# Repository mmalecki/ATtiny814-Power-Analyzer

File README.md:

# Pocker Power Prowler

**Note: this is still very much a work in progress, and next version will bring considerable improvements over the current one.**

Pocket Power Prowler is a tiny programmable constant current dummy load with voltage and current sensors for test device's power supply, as well as its output under test.

It is programmable via USB using a simple text-based protocol, and [in the future](https://github.com/mmalecki/Pocket-Power-Prowler/issues/4)), the [SCPI protocol](https://en.wikipedia.org/wiki/Standard_Commands_for_Programmable_Instruments).

It is based on the [ATtiny814 Power Analyzer](https://github.com/wagiminator/ATtiny814-Power-Analyzer) by [@wagiminator](https://github.com/wagiminator/ATtiny814-Power-Analyzer).
If you're interested in how the project changed, check out the [changelog](CHANGELOG.md).

The overarching goal of the project is to create a portable, accurate, reliable and safe dummy load.

# Current control
Current control is implemented using the ATtiny814's digital-to-analog converter (DAC), a level-shifting operational amplifier
(OpAmp) as well as [INA219](https://www.ti.com/lit/ds/symlink/ina219.pdf) current sensor connected to a 8mΩ shunt resistor.

While running a test, software on the ATtiny constantly compares the desired current set by user with current reported by
the sensor, and makes adjustments to the DAC output as necessary, in turn controlling the gate voltage of a
[IRL540N](https://datasheet.lcsc.com/lcsc/1808281632_Infineon-Technologies-IRL540NPBF_C111607.pdf) logic level
power MOSFET, which adjusts its resistance, therefore changing the current flowing and being dissipated through it.

## DAC and OpAmp

The resistor values (for gain and voltage offset) were picked so that when ATtiny outputs 0 V on its DAC output,
the voltage at the gate of MOSFET is just below its turning on point (V<sub>GS</sub>), and when ATtiny outputs the full
DAC voltage at our picked reference point (1.5 V), the MOSFET is conducting the full amount of current we're
equipped to handle (5 A). In short, we're looking for the (almost entire) range of the DAC to cover the (almost entire)
ohmic region of the MOSFET.

## Current sensor and current control loop
On a set interval (currently 5 ms), the ATtiny reads current levels from the load-side INA219 sensor, compares them to set value
and reacts accordingly if the current differs from the setpoint.

This is necessary due to inherently nonlinear characteristics of any MOSFET, changing with voltages, currents and temperatures affecting it.

## Compiling and Uploading the Firmware

### If using the makefile (Linux/Mac)
- Connect your [programmer](https://github.com/wagiminator/AVR-Programmer) (jtag2updi or SerialUPDI) to your PC and to the UPDI header on the board.
- Make sure you have installed the latest [avr-gcc toolchain](http://maxembedded.com/2015/06/setting-up-avr-gcc-toolchain-on-linux-and-mac-os-x/).
- Open a terminal.
- Navigate to the folder with the makefile and the sketch.
- Run `DEVICE=attiny814 PROGRMR=serialupdi PORT=/dev/ttyUSB0 make install` to compile, burn the fuses and upload the firmware (change DEVICE, PROGRMR and PORT accordingly).

# Operating Instructions
The device can be operated in two ways:
- Using a serial monitor: Test algorithms can be started by sending the corresponding command via a serial monitor. The collected data will be displayed in the serial monitor and can be exported to a spread sheet program for further analysis.
- Using the [web app](...). This is the easy way. Everything should be self-explanatory. All following example pictures are created by this application.

## **Load Test**

- Command: "l  *maxloadcurrent[mA: 0..5000]* *minloadvoltage[mV: 0..26000]*"
- Example: "l 2500 4200"
- Prowler continuously increases the load from 0 mA up to *maxloadcurrent*. It stops automatically if the voltage drops below *minloadvoltage*. It continuously transmits the measured values via the serial interface in the format: `current[mA] voltage[mV] power[mW]` (seperated by the `SEPERATOR` character).

## **Voltage Regulation Test**

- Command: "g *maxloadcurrent[mA: 17..5000]*"
- Example: "g 3000"
- The Power Analyzer changes rapidly the load between 17 mA and *maxloadcurrent*. It continuously transmits the measured values via the serial interface in the format: time[ms] current[mA] voltage[mV] (seperated by the SEPERATOR string).

## **Efficiency Test**

- Command: "e  *maxloadcurrent[mA: 17..5000]* *minloadvoltage[mV: 0..26000]*"
- Example: "e 4000 2500"
- The Power Analyzer continuously increases the load from 17 mA up to *maxloadcurrent*. It stops automatically if the voltage at TEST-IN drops below *minloadvoltage*. It continuously transmits the measured values via the serial interface in the format: current[mA] voltage[mV] efficiency[% * 10] (seperated by the SEPERATOR string).

## **Battery Discharge Test**

- Command: "b  *maxloadcurrent[mA: 17..5000]* *minloadvoltage[mV: 0..26000]*"
- Example: "l 1000 2700"
- The Power Analyzer sets a constant current load of *maxloadcurrent*. If the voltage drops below *minloadvoltage* it constantly decreases the load to maintain *minloadvoltage*. It stops automatically if the load current drops to 0mA. It continuously transmits the measured values via the serial interface in the format: time[s] current[mA] voltage[mV] capacity[mAh] (seperated by the SEPERATOR string).

## **Long-Term Multimeter**

- Command: "m  *interval[ms: 2..65535]* *duration[s: 1..65535]*"
- Example: "m 18000 18000"
- The Power Analyzer measures voltage, current and power delivered to the test device at every *interval* for a total of *duration*. It continuously transmits the measured values via the serial interface in the format: time[ms] current[mA] voltage[mV] (seperated by the SEPERATOR string).

## **Commands for Direct Control**
|Command|Function|
|-|-|
|"i"|transmits indentification string ("Power Analyzer")|
|"v"|transmits firmware version number|
|"x"|terminate current test program, reset load to minimum|
|"s *loadcurrent[mA]*"|set load to a constant current of *loadcurrent*|
|"t"|read current and voltage of both sensors and transmit them|

# Notes
- Use a good heatsink with a fan for the MOSFET! Attach a 10K 3977B or 3950B (configurable in code) NTC thermistor to the heatsink close to the MOSFET!
- Be careful with high power loads! Make some tests to figure out what can be achieved with your cooling solution!
- The maximum load current is 5A, however for small voltages it might be less.
- The maximum PWR-IN/PWR-OUT current is 8A.
- Do not exceed the maximum voltage of 26V on all connectors!
- In order to make the design much simpler all connectors including USB share a common ground. Keep this in mind when making your test setup in order to avoid ground loops or shorts. Using a [USB isolator](https://github.com/wagiminator/ADuM3160-USB-Isolator) between the Analyzer and your PC is not a bad idea!
- You need a UPDI programmer for uploading the firmware. You can find one in my [projects](https://github.com/wagiminator/AVR-Programmer) or you can easily build one following this [guide](https://github.com/SpenceKonde/AVR-Guidance/blob/master/UPDI/jtag2updi.md).

# License

This work is licensed under Creative Commons Attribution-ShareAlike 3.0 Unported License. 
(http://creativecommons.org/licenses/by-sa/3.0/)

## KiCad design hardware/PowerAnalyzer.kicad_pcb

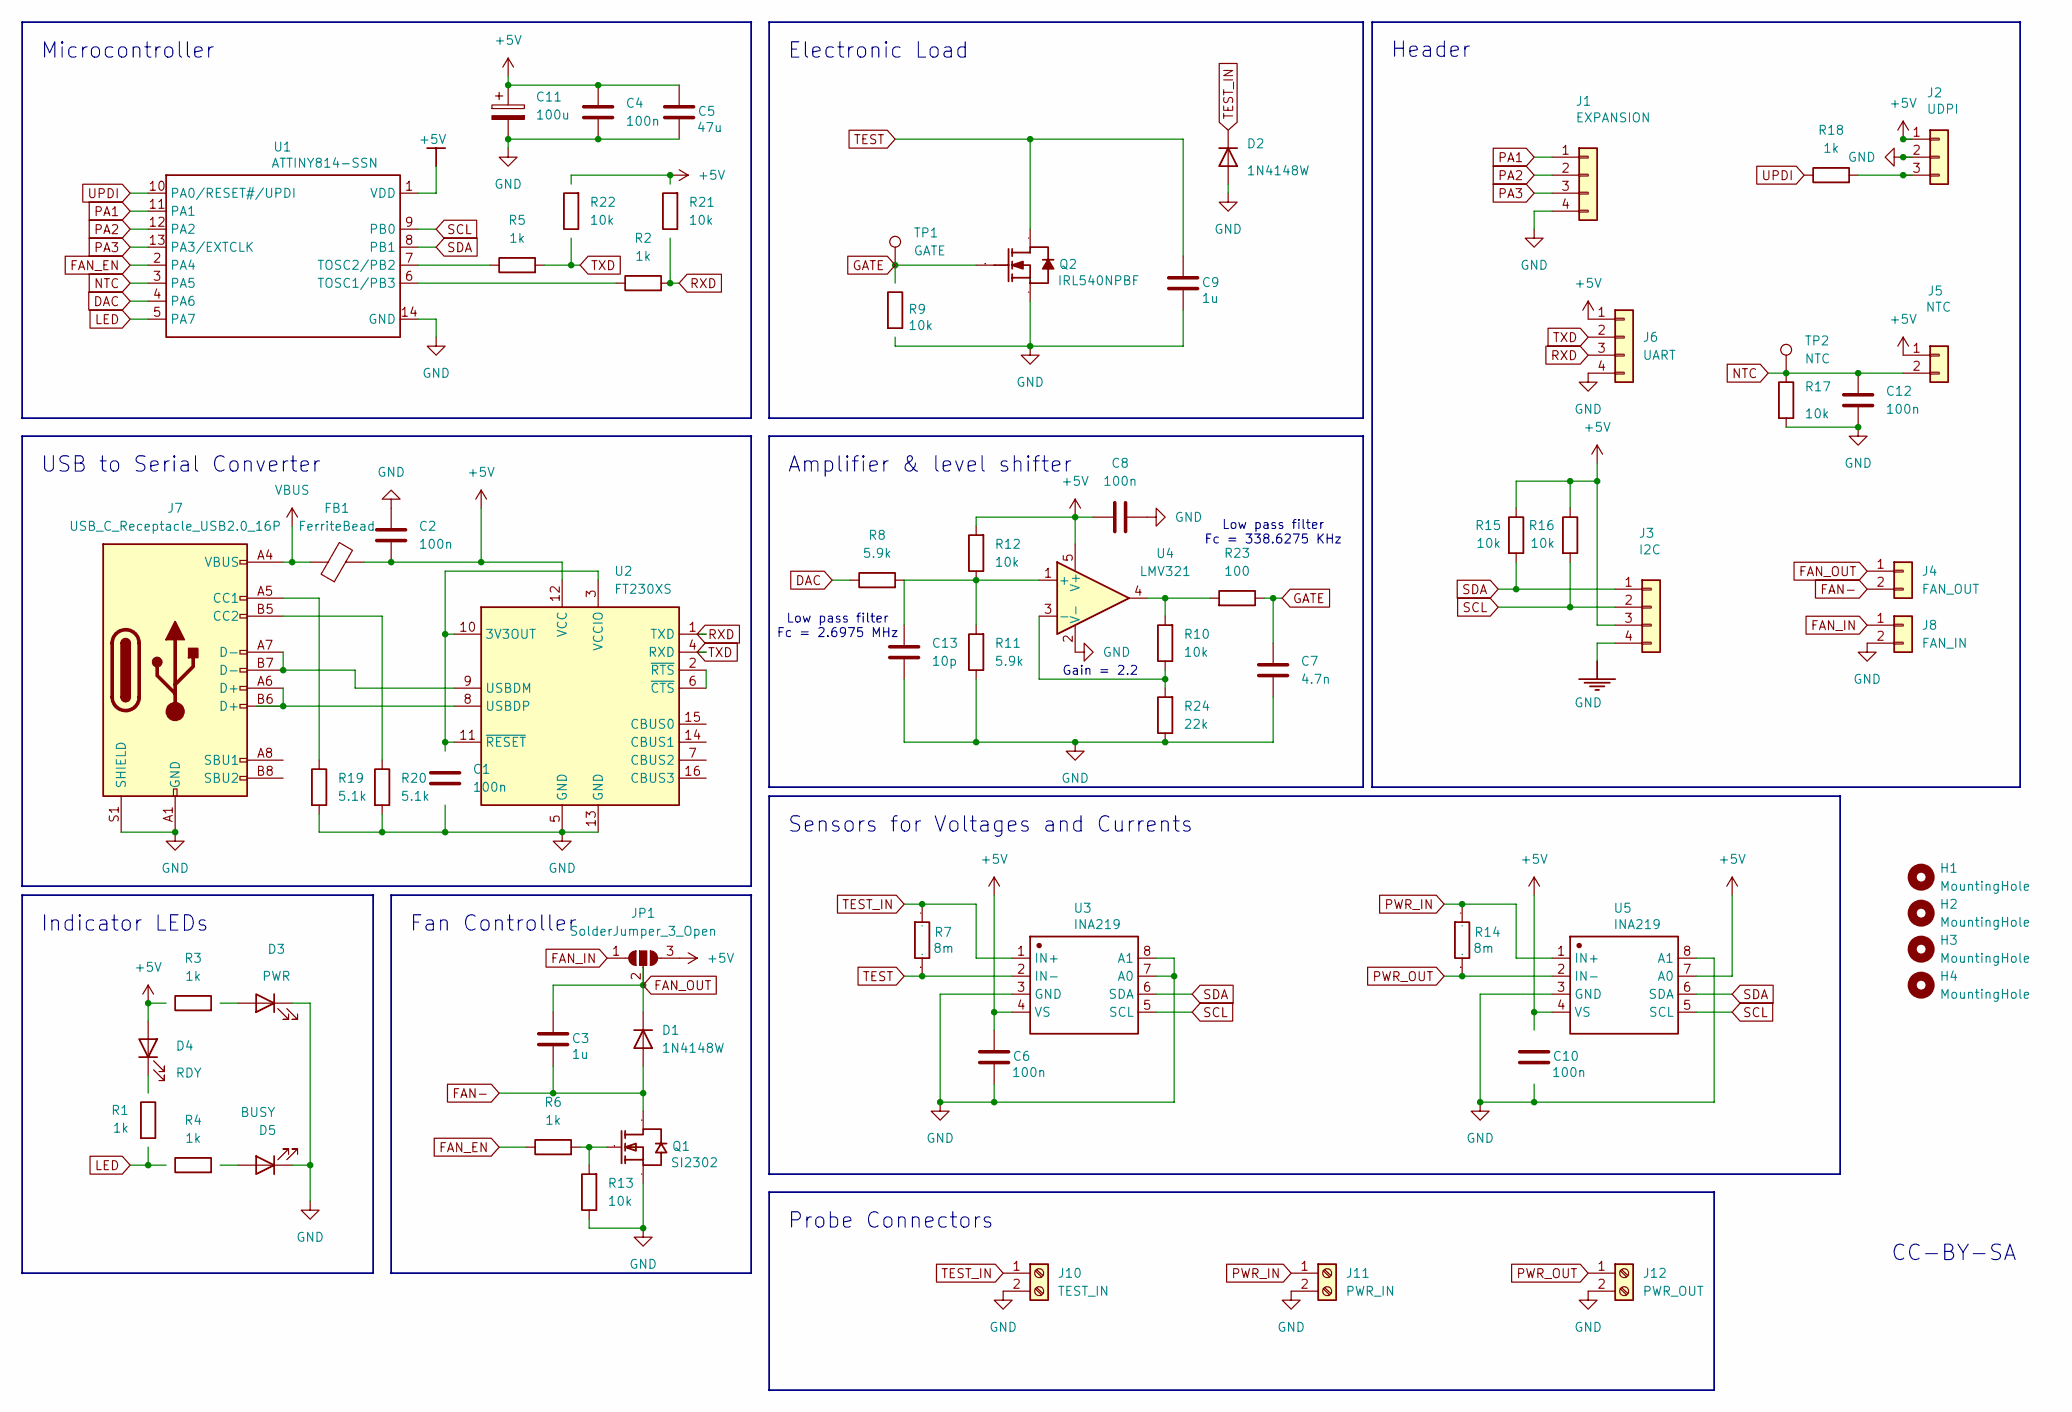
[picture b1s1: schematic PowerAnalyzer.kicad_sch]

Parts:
C1, C2, C4, C6, C8, C10, C12: 100n; C_0603_1608Metric; Manufacturer Part CC0603KRX7R9BB104
C3, C9: 1u; C_0603_1608Metric; Voltage 50V; Manufacturer Part CL10A105KB8NNNC
C5: 47u; C_1206_3216Metric; Manufacturer Part 1206F476M160NT
C7: 4.7n; C_0603_1608Metric
C11: 100u; CP_Radial_D5.0mm_P2.00mm
C13: 10p; C_0603_1608Metric
D1, D2: 1N4148W; D_SOD-123; Manufacturer Part 1N4148W-E3-08
D3: PWR; LED_0603_1608Metric; Manufacturer Part 19-217/BHC-ZL1M2RY/3T
D4: RDY; LED_0603_1608Metric; Manufacturer Part 19-217/BHC-ZL1M2RY/3T
D5: BUSY; LED_0603_1608Metric; Manufacturer Part 19-217/BHC-ZL1M2RY/3T
FB1: FerriteBead; L_0603_1608Metric; Manufacturer Part BLM18EG121SN1D
H1, H2, H3, H4: MountingHole; MountingHole_2.2mm_M2
J1: EXPANSION; PinHeader_1x04_P2.54mm_Vertical; Manufacturer Part 220S-1*4P H=8.5MM Ytype Gold-plated
J2: UDPI; PinHeader_1x03_P2.54mm_Vertical; Manufacturer Part Header2.54mm 1*3P
J3: I2C; PinHeader_1x04_P2.54mm_Vertical; Manufacturer Part 220S-1*4P H=8.5MM Ytype Gold-plated
J4: FAN_OUT; PinHeader_1x02_P2.54mm_Vertical
J5: NTC; PinHeader_1x02_P2.54mm_Vertical; Manufacturer Part 826629-2
J6: UART; PinHeader_1x04_P2.54mm_Vertical
J7: USB_C_Receptacle_USB2.0_16P; USB_C_Receptacle_GCT_USB4105-xx-A_16P_TopMnt_Horizontal
J8: FAN_IN; PinHeader_1x02_P2.54mm_Vertical
J10: TEST_IN; TerminalBlock_Xinya_XY301V-5.00-2P_1x02_P5.00mm_Horizontal; Manufacturer Part KF301R-5.0-2P
J11: PWR_IN; TerminalBlock_Xinya_XY301V-5.00-2P_1x02_P5.00mm_Horizontal; Manufacturer Part KF301R-5.0-2P
J12: PWR_OUT; TerminalBlock_Xinya_XY301V-5.00-2P_1x02_P5.00mm_Horizontal; Manufacturer Part KF301R-5.0-2P
JP1: SolderJumper_3_Open; SolderJumper-3_P1.3mm_Open_RoundedPad1.0x1.5mm
Q1: SI2302; SOT-23-3; Manufacturer Part SI2302
Q2: IRL540NPBF; TO-220-3_Vertical; Manufacturer Part IRL540NPBF
R1, R2, R3, R4, R5, R6: 1k; R_0603_1608Metric; Manufacturer Part 0603WAF1001T5E
R7, R14: 8m; R_2512_6332Metric; Manufacturer Part MRF6432(2512)LR008FTS
R8: 5.9k; R_0603_1608Metric
R9, R10, R12, R17, R21, R22: 10k; R_0603_1608Metric; Manufacturer Part 0603WAF1002T5E
R11: 5.9k; R_0603_1608Metric; Manufacturer Part 0603WAF1002T5E
R13: 10k; R_0603_1608Metric; Manufacturer Part 0603WAF1001T5E
R15, R16: 10k; R_0603_1608Metric; Manufacturer Part 0603WAF4701T5E
R18: 1k; R_0603_1608Metric; Manufacturer Part 0603WAF4701T5E
R19, R20: 5.1k; R_0603_1608Metric
R23: 100; R_0603_1608Metric
R24: 22k; R_0603_1608Metric
TP1: GATE; TestPoint_Pad_D1.0mm
TP2: NTC; TestPoint_Pad_D1.0mm
U1: ATTINY814-SSN; SOIC-14_3.9x8.7mm_P1.27mm; Manufacturer Part ATTINY814-SSNR
U2: FT230XS; SSOP-16_3.9x4.9mm_P0.635mm
U3, U5: INA219; SOT-23-8; Manufacturer Part INA219AIDCNR
U4: LMV321; SOT-23-5

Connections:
+5V: C2.1, C4.1, C5.1, C6.1, C8.1, C10.1, C11.1, D4.2 (A), FB1.2, J2.1, J3.3, J5.1, J6.1, JP1.3 (B), R3.1, R12.2, R15.1, R16.1, R21.2, R22.2, U1.1 (VDD), U2.12 (VCC), U3.4 (VS), U4.5 (V+), U5.4 (VS), U5.7 (A0)
DAC: R8.1, U1.4 (PA6)
FAN-: C3.2, D1.2 (A), J4.2, Q1.3 (D)
FAN_EN: R6.1, U1.2 (PA4)
FAN_IN: J8.1, JP1.1 (A)
FAN_OUT: C3.1, D1.1 (K), J4.1, JP1.2 (C)
GATE: C7.1, Q2.1 (G), R9.1, R23.1, TP1.1
GND: C1.1, C2.2, C4.2, C5.2, C6.2, C7.2, C8.2, C9.2, C10.2, C11.2, C12.1, C13.2, D2.2 (A), D3.1 (K), D5.1 (K), J1.4, J2.2, J3.4, J6.4, J7.A1 (GND), J7.A12 (GND), J7.B1 (GND), J7.B12 (GND), J7.S1 (SHIELD), J8.2, J10.2, J11.2, J12.2, Q1.2 (S), Q2.3 (S), R9.2, R11.1, R13.1, R17.2, R19.2, R20.2, R24.1, U1.14 (GND), U2.5 (GND), U2.13 (GND), U3.3 (GND), U3.7 (A0), U3.8 (A1), U4.2 (V-), U5.3 (GND), U5.8 (A1)
LED: R1.2, R4.1, U1.5 (PA7)
NTC: C12.2, J5.2, R17.1, TP2.1, U1.3 (PA5)
unnamed: D3.2 (A), R3.2
unnamed: D4.1 (K), R1.1
unnamed: D5.2 (A), R4.2
unnamed: J2.3, R18.2
unnamed: J7.A5 (CC1), R19.1
unnamed: J7.B5 (CC2), R20.1
unnamed: Q1.1 (G), R6.2, R13.2
unnamed: R10.2, R23.2, U4.4
unnamed: R2.1, U1.6 (TOSC1/PB3)
unnamed: R5.1, U1.7 (TOSC2/PB2)
unnamed: J7.A7 (D-), J7.B7 (D-), U2.9 (USBDM)
unnamed: J7.A6 (D+), J7.B6 (D+), U2.8 (USBDP)
unnamed: U2.2 (~RTS), U2.6 (~CTS)
unnamed: C13.1, R8.2, R11.2, R12.1, U4.1 (+)
unnamed: R10.1, R24.2, U4.3 (-)
PA1: J1.1, U1.11 (PA1)
PA2: J1.2, U1.12 (PA2)
PA3: J1.3, U1.13 (PA3/EXTCLK)
PWR_IN: J11.1, R14.2, U5.1 (IN+)
PWR_OUT: J12.1, R14.1, U5.2 (IN-)
RXD: J6.3, R2.2, R21.1, U2.1 (TXD)
SCL: J3.2, R16.2, U1.9 (PB0), U3.5 (SCL), U5.5 (SCL)
SDA: J3.1, R15.2, U1.8 (PB1), U3.6 (SDA), U5.6 (SDA)
TEST: C9.1, Q2.2 (D), R7.1, U3.2 (IN-)
TEST_IN: D2.1 (K), J10.1, R7.2, U3.1 (IN+)
TXD: J6.2, R5.2, R22.1, U2.4 (RXD)
UPDI: R18.1, U1.10 (PA0/RESET#/UPDI)
VBUS: FB1.1, J7.A4 (VBUS), J7.A9 (VBUS), J7.B4 (VBUS), J7.B9 (VBUS)

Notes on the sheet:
USB to Serial Converter
Sensors for Voltages and Currents
Indicator LEDs
Header
Gain = 2.2
Microcontroller
CC-BY-SA
Low pass filter Fc = 338.6275 KHz
Amplifier & level shifter
Electronic Load
Low pass filter Fc = 2.6975 MHz
Fan Controller
Probe Connectors

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
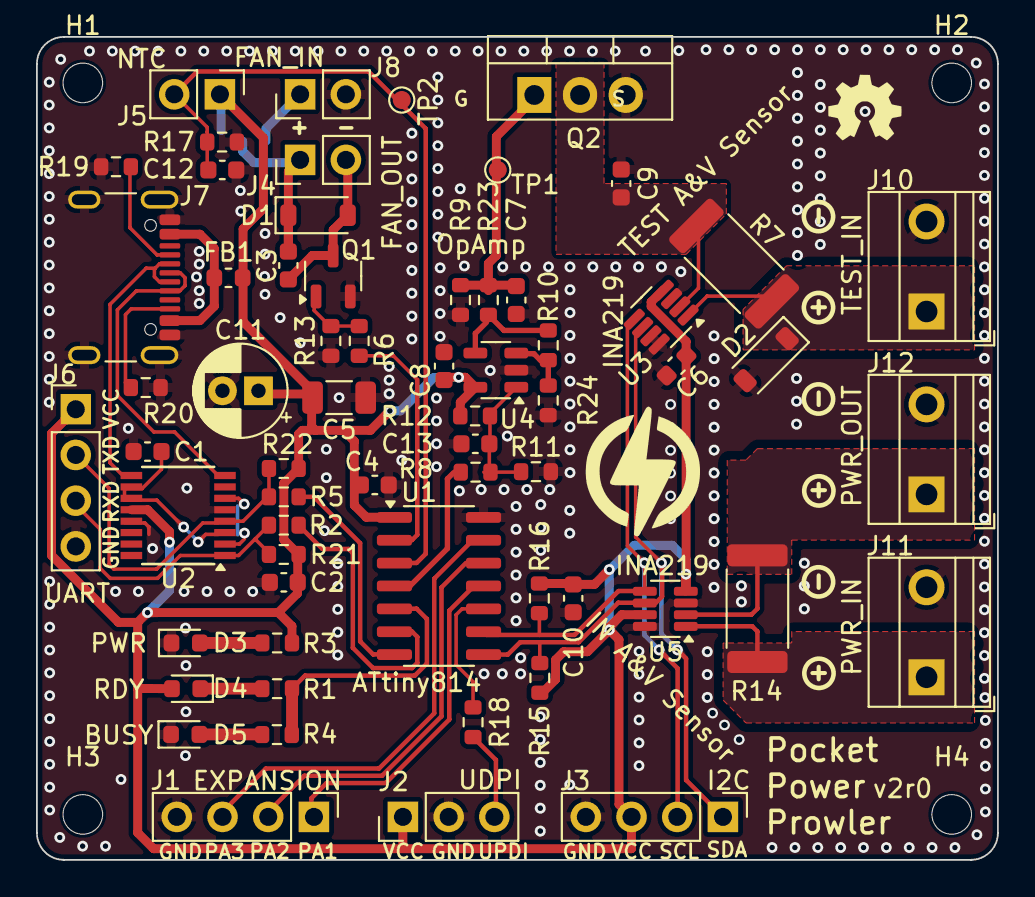
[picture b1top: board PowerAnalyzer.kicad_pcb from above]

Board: 2 copper layers, 53.4 x 45.7 mm, 68 parts (1 on the bottom side), 39 nets.

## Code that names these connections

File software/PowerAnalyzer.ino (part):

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// -------
//                            +-\/-+
//                      Vcc  1|°   |14  GND
//     Fan --- !SS AIN4 PA4  2|    |13  PA3 AIN3 SCK ---- 
//     NTC ------- AIN5 PA5  3|    |12  PA2 AIN2 MISO --- 
//    Load --- DAC AIN6 PA6  4|    |11  PA1 AIN1 MOSI --- 
//     LED ------- AIN7 PA7  5|    |10  PA0 AIN0 UPDI --- UPDI
//     USB -------- RXD PB3  6|    |9   PB0 AIN11 SCL --- INA219
//     USB ---------TXD PB2  7|    |8   PB1 AIN10 SDA --- INA219
//                            +----+
//
// Compilation Settings:
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#include <util/delay.h>                 // for delays

// Pin definitions
#define FAN_PIN     PA4                 // pin the fan is connected to
#define NTC_PIN     PA5                 // pin the temperature sensor is connected to
#define DAC_PIN     PA6                 // DAC output pin, connected to load
#define LED_PIN     PA7                 // pin the status LED is connected to
#define SCL_PIN     PB0                 // I2C serial clock pin, connected to INA219
#define SDA_PIN     PB1                 // I2C serial data pin, connected to INA219
#define TXD_PIN     PB2                 // UART transmit data pin, connected to CH330N
#define RXD_PIN     PB3                 // UART receive data pin, connected to CH330N

// Identifiers
#define VERSION     "1.1"               // version number sent via serial if requested
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#define MAXPOWER    25000               // maximum power of the load in mW -> turn off load
#define FANONPOWER  700                 // power in mW to turn fan on
#define FANOFFPOWER 500                 // power in mW to turn fan off
#define MAXTEMP     820                 // max ADC-value of NTC_PIN -> turn off load
#define FANONTEMP   585                 // ADC-value of NTC_PIN to turn fan on
#define FANOFFTEMP  540                 // ADC-value of NTC_PIN to turn fan off
#define SETTLE      25                  // settle time in ms

// INA219 register values
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#define CURRENT_REG 0x04                // INA current register address

// Pin manipulation macros
enum {PA0, PA1, PA2, PA3, PA4, PA5, PA6, PA7, PB0, PB1, PB2, PB3};    // enumerate pin designators
#define pinInput(x)       (&VPORTA.DIR)[((x)&8)>>1] &= ~(1<<((x)&7))  // set pin to INPUT
#define pinOutput(x)      (&VPORTA.DIR)[((x)&8)>>1] |=  (1<<((x)&7))  // set pin to OUTPUT
#define pinLow(x)         (&VPORTA.OUT)[((x)&8)>>1] &= ~(1<<((x)&7))  // set pin to LOW
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
  // Calculate load power and read temperature of the heatsink
  loadpower= ((uint32_t)voltage1 * current1 + 500) / 1000;
  loadtemp = ADC_read(pinAIN(NTC_PIN));

  // Turn fan on or off depending on load power and temperature
  if((loadpower > MAXPOWER)    || (loadtemp > MAXTEMP))    DAC_resetLoad();
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  // Setup pins
  pinOutput(FAN_PIN);                             // set fan pin as output
  pinOutput(LED_PIN);                             // set LED pin as output
  pinDisable(NTC_PIN);                            // disable digital input buffer

  // Loop
  while(1) {
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
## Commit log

2024-07-07 Remove old output files
2024-07-07 Add a KiCad .gitignore
2024-07-07 Ignore outputs
2024-07-07 Import to KiCad, migrate to USB C
    Stitch some vias.
    Use a FT230, expose UART for use with external converters (e.g.
    Flipper).
2024-07-28 Fix diodes
    Their pins are numbered differently on easyEDA.
    Move some vias which may cause tombstoning.
2024-07-28 Include `.rodata` section
2024-07-28 Ignore and remove built files
2024-07-28 Use stock tools
    Switch to `avrdude` by default, as `pymcuprog` did not work for me.
2024-07-28 Use a single character separator
    This saves plenty of flash.
2024-07-28 Make LED management a little easier
2024-07-28 This is not a sketch
2024-07-28 Implement UART loopback and debug facilities
    Further separator changes.
2024-07-28 Start refactoring temperature handling
    Approximate the NTC temperature using its Beta coefficient.
    Start implementing centralized logic for over-heating and -power.
2024-07-30 Improve thermal behavior
    Calculate temperature based on NTC Beta value.
    Allow turning fans on and off manually, as well as automatically.
    Handle overload while refreshing load sensors instead of in every test
    function separately. This saves us sizable flash space.
    Have 'x' reset load in the menu.
2024-07-31 Pocket Power Prowler v2
    Migrate from semi-constant current control via shunt and operational
    amplifier to direct DAC- and P[ID]-based control algorithm.
    Bias the op amp just below the MOSFET threshold voltage to make use of
    full DAC range.
    Reduce DAC output capacitance from 100 n to 10 p (in order to filter out
    high frequencies coming from DAC peripheral clock).
2024-08-10 Allow disabling NTC for testing purposes
    Otherwise we're just spewing infinite OVERLOAD messages due to the
    sensor having infinite resistance if unplugged.
2024-08-10 Finish (?) KiCadifying
2024-08-10 wip: scpi, attiny too small
2024-08-12 Implement incredibly basic error correction based on current reading
    Remove the multimeter (`m`) command and add optional time parameters to
    transmit sensors (`s`).
2024-08-12 Use tried and tested values
    Rework on that opamp section sure was fun.
2024-08-12 Add a preliminary changelog
2024-08-12 Report last step in load test
2024-08-12 Move the transistor a bit to the right
    Allow more space for the heatsink.
2024-08-13 Disable UART echoback by default
2024-08-13 Start implementing a web GUI
2024-08-13 Add a missing change to CHANGELOG
2024-08-13 Limit maximum current to 4999 mA
2024-08-13 Continue adding items to changelog
2024-08-13 Run control loop on step interval, not report interval when load testing
2024-08-13 Support querying commands
2024-08-15 Increase the range of load-side INA219 current sensor
2024-09-11 Add a v2r0 case
2024-09-11 Add a top view
2024-09-11 Add the opamp simulation project
2024-09-11 Pocket Power Prowler!
2024-09-11 Mention the ferrite bead
2024-09-11 More documentation in the schematic
2024-09-11 Describe reasoning behind current control changes
2024-09-11 Fresh main picture
2024-09-11 Introduce a P controller
2024-09-11 Output PCB step file for case visualizations
2024-09-11 Add the opamp screenshot
2024-09-11 Mount the new cooling solution
2024-09-11 Remove the `DRCError` layer
2024-11-14 Fix layer names to KiCad
2024-11-14 Specify `.svg` output path as `out/`
